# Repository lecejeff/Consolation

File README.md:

# Consolation
Consolation [Console Emulation] project goal is to create a portable emulation device 100% open-source and designed for cost effectiveness and accessibility.

Based on Raspberry Pi Compute Module 5 as core processor

Based on Raspberry Pi RP2350A as joystick controller re-using GP2040-CE FW

Based on Texas Instruments BQ25640 as USB-C PD solution and battery charger

Based on Nuvoton NAU88C22 audio codec

Consolation is a french word for:

1 : the act or an instance of consoling : the state of being consoled : comfort

2 : something that consoles

## SPONSOR

This project is proudly sponsored by [NextPCB](https://www.nextpcb.com). They have provided, free of charge, 2x assembled PCBA, as part of NextPCB accelerator program.

If you’re planning to build your own PCB, [NextPCB](https://www.nextpcb.com) offers reliable PCB fabrication and assembly services with fast turnaround times and competitive pricing, making it easier to bring your electronics projects from idea to reality.
NextPCB provides a free DFM software called NextDFM, which became, honestly, an essential tool in my toolbox, and should be the same for any serious hobbyist trying to limit PCB revisions, production back and forth, and confirm manufacturability of a design. 
NextDFM analyzes gerbers, checks Pick N Place data, validates component alignment (origin) against PnP data, validates BOM accuracy against PnP data... And also performs DFM checks for manufacturability. It's really an amazing software and it's free.

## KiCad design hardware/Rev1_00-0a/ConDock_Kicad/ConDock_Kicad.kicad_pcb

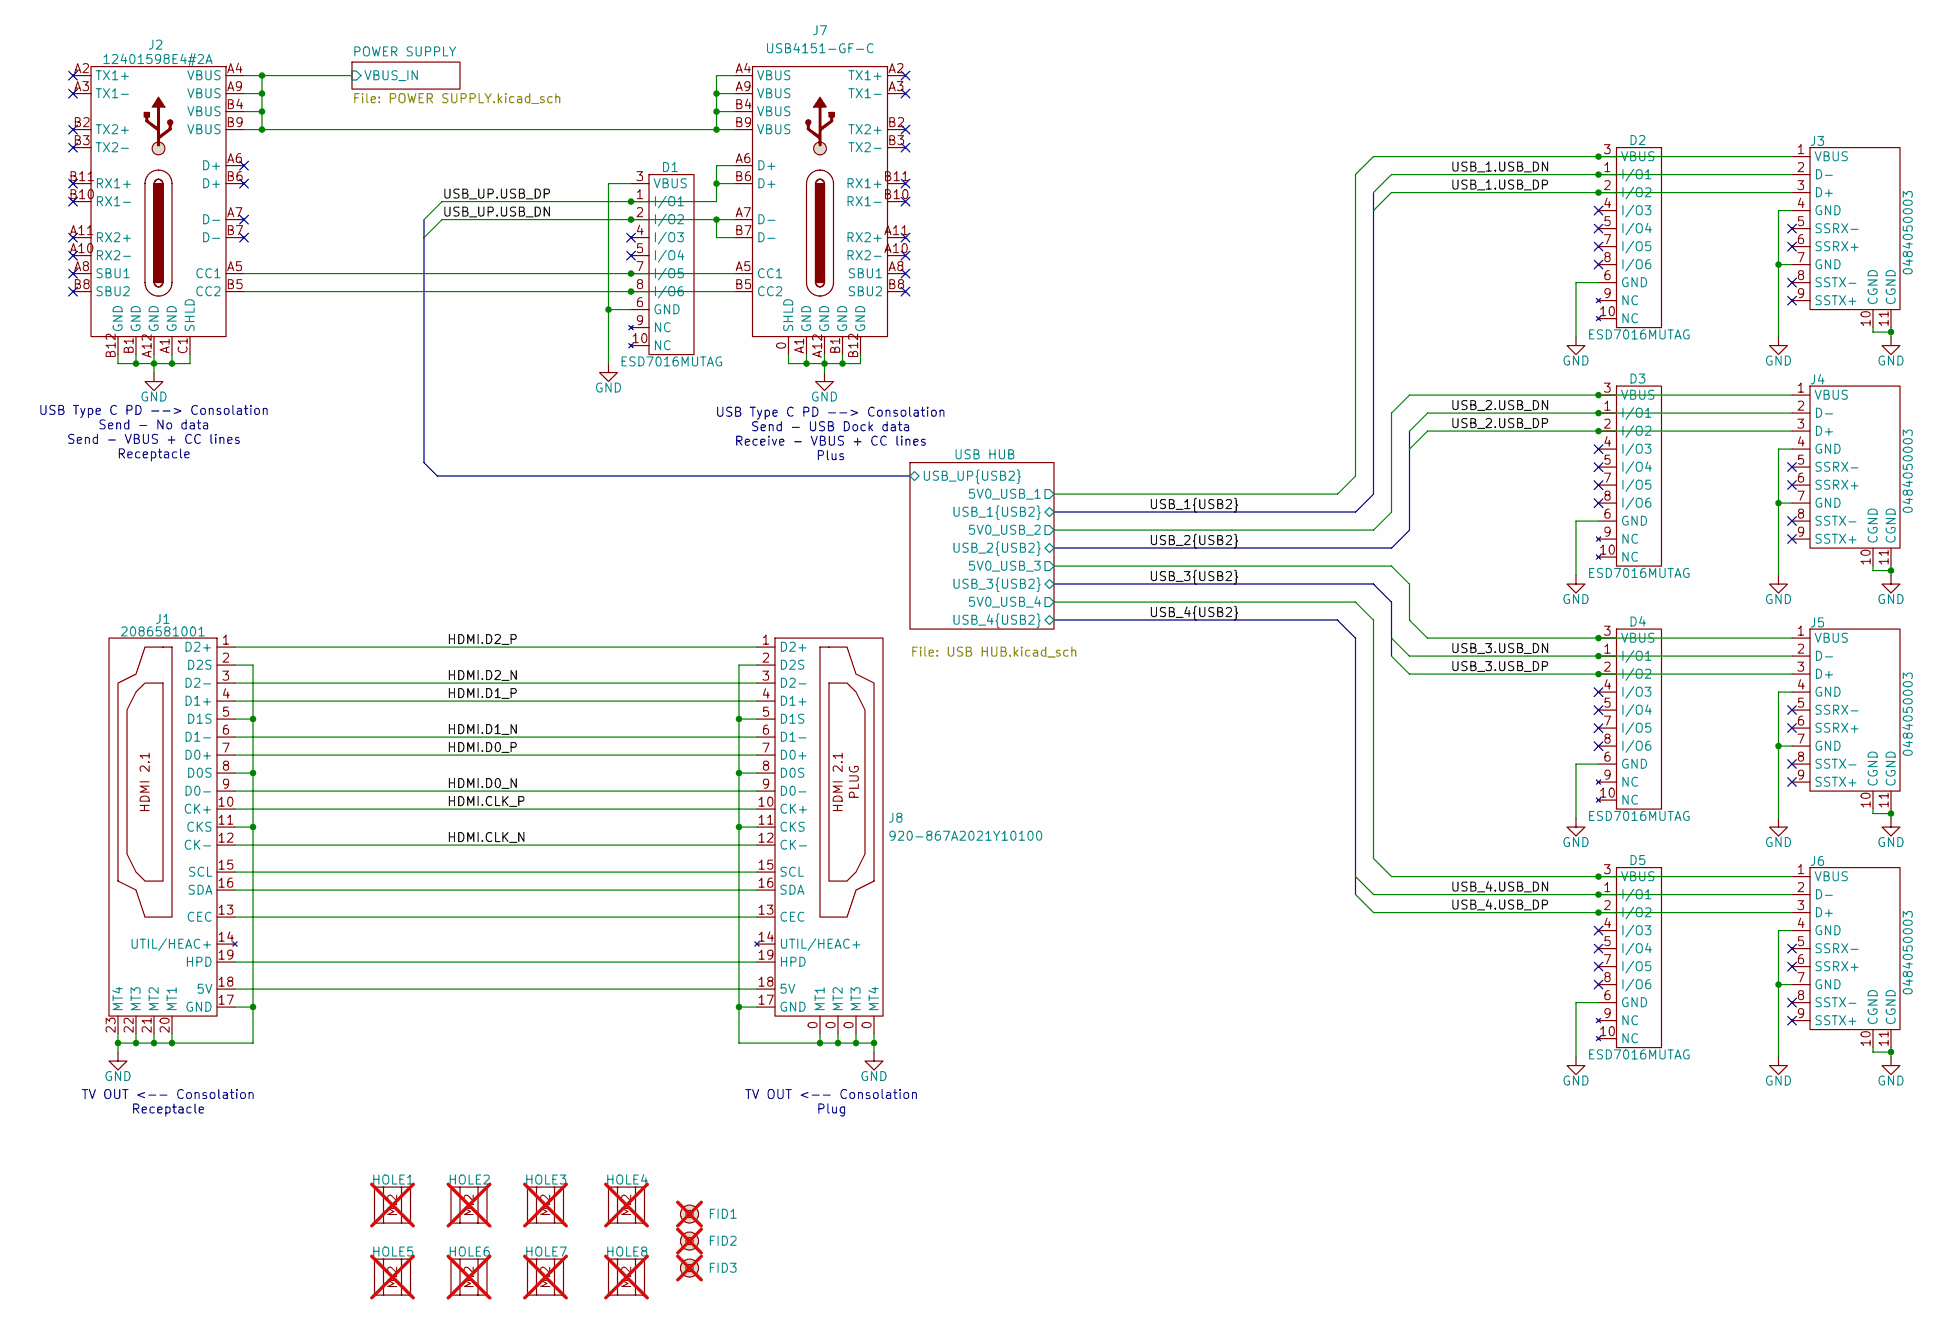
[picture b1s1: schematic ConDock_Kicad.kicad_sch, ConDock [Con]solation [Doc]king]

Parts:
D1, D2, D3, D4, D5: ESD7016MUTAG; UDFN8; Manufacturer Part Number ESD7016MUTAG
FID1, FID2, FID3: FIDUCIAL; not fitted
HOLE1, HOLE2, HOLE3, HOLE4, HOLE5, HOLE6, HOLE7, HOLE8: NPTH_M2; not fitted
J1: 2086581001; Current Rating 0.5A; Voltage Rating 40V; Manufacturer Part Number 2086581001
J2: 12401598E4#2A; Current Rating 5A; Voltage Rating 100V; Manufacturer Part Number 12401598E4#2A
J3, J4, J5, J6: 0484050003; Current Rating 1.8A; Voltage Rating 30V; Manufacturer Part Number 0484050003
J7: USB4151-GF-C; Current Rating 5A; Voltage Rating 48V; Manufacturer Part Number USB4151-GF-C
J8: 920-867A2021Y10100; Current Rating 0.5A; Voltage Rating 40V; Manufacturer Part Number 920-867A2021Y10100

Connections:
/HDMI.CLK_N: J1.12 (CK-), J8.12 (CK-)
/HDMI.CLK_P: J1.10 (CK+), J8.10 (CK+)
/HDMI.D0_N: J1.9 (D0-), J8.9 (D0-)
/HDMI.D0_P: J1.7 (D0+), J8.7 (D0+)
/HDMI.D1_N: J1.6 (D1-), J8.6 (D1-)
/HDMI.D1_P: J1.4 (D1+), J8.4 (D1+)
/HDMI.D2_N: J1.3 (D2-), J8.3 (D2-)
/HDMI.D2_P: J1.1 (D2+), J8.1 (D2+)
/POWER SUPPLY/VBUS_IN: J2.A4 (VBUS), J2.A9 (VBUS), J2.B4 (VBUS), J2.B9 (VBUS), J7.A4 (VBUS), J7.A9 (VBUS), J7.B4 (VBUS), J7.B9 (VBUS); also elsewhere on the board
/USB HUB/5V0_USB_1: D2.3 (VBUS), J3.1 (VBUS); also elsewhere on the board
/USB HUB/5V0_USB_2: D3.3 (VBUS), J4.1 (VBUS); also elsewhere on the board
/USB HUB/5V0_USB_3: D4.3 (VBUS), J5.1 (VBUS); also elsewhere on the board
/USB HUB/5V0_USB_4: D5.3 (VBUS), J6.1 (VBUS); also elsewhere on the board
/USB HUB/USB_UP.USB_DN: D1.2 (I/O2), J7.A7 (D-), J7.B7 (D-); also elsewhere on the board
/USB HUB/USB_UP.USB_DP: D1.1 (I/O1), J7.A6 (D+), J7.B6 (D+); also elsewhere on the board
/USB_1.USB_DN: D2.1 (I/O1), J3.2 (D-); also elsewhere on the board
/USB_1.USB_DP: D2.2 (I/O2), J3.3 (D+); also elsewhere on the board
/USB_2.USB_DN: D3.1 (I/O1), J4.2 (D-); also elsewhere on the board
/USB_2.USB_DP: D3.2 (I/O2), J4.3 (D+); also elsewhere on the board
/USB_3.USB_DN: D4.1 (I/O1), J5.2 (D-); also elsewhere on the board
/USB_3.USB_DP: D4.2 (I/O2), J5.3 (D+); also elsewhere on the board
/USB_4.USB_DN: D5.1 (I/O1), J6.2 (D-); also elsewhere on the board
/USB_4.USB_DP: D5.2 (I/O2), J6.3 (D+); also elsewhere on the board
GND: D1.3 (VBUS), D1.6 (GND), D2.6 (GND), D3.6 (GND), D4.6 (GND), D5.6 (GND), J1.2 (D2S), J1.5 (D1S), J1.8 (D0S), J1.11 (CKS), J1.17 (GND), J1.20 (MT1), J1.21 (MT2), J1.22 (MT3), J1.23 (MT4), J2.A1 (GND), J2.A12 (GND), J2.B1 (GND), J2.B12 (GND), J2.C1 (SHLD), J3.4 (GND), J3.7 (GND), J3.10 (CGND), J3.11 (CGND), J4.4 (GND), J4.7 (GND), J4.10 (CGND), J4.11 (CGND), J5.4 (GND), J5.7 (GND), J5.10 (CGND), J5.11 (CGND), J6.4 (GND), J6.7 (GND), J6.10 (CGND), J6.11 (CGND), J7.0 (SHLD), J7.A1 (GND), J7.A12 (GND), J7.B1 (GND), J7.B12 (GND), J8.0 (MT4), J8.2 (D2S), J8.5 (D1S), J8.8 (D0S), J8.11 (CKS), J8.17 (GND); also elsewhere on the board
unnamed: D1.7 (I/O5), J2.A5 (CC1), J7.A5 (CC1)
unnamed: D1.8 (I/O6), J2.B5 (CC2), J7.B5 (CC2)
unnamed: J1.18 (5V), J8.18 (5V)
unnamed: J1.13 (CEC), J8.13 (CEC)
unnamed: J1.19 (HPD), J8.19 (HPD)
unnamed: J1.15 (SCL), J8.15 (SCL)
unnamed: J1.16 (SDA), J8.16 (SDA)

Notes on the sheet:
USB Type C PD --> Consolation Send - USB Dock data Receive - VBUS + CC lines Plus
TV OUT <-- Consolation Receptacle
TV OUT <-- Consolation Plug
USB Type C PD --> Consolation Send - No data Send - VBUS + CC lines Receptacle

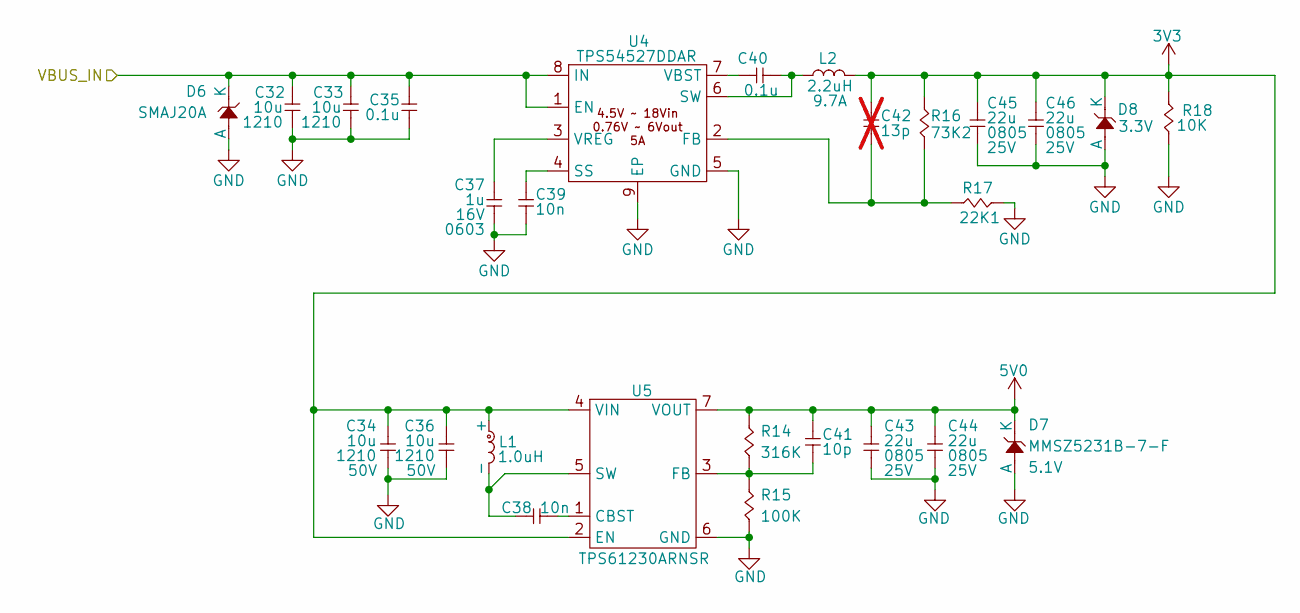
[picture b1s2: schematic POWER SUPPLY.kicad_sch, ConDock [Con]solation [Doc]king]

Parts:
C32, C33: 10u; CAP_NONPOL_1210; Tolerance ±10%; Voltage Rating 50V; Manufacturer Part Number C3225X7R1H106K250AC
C34, C36: 10u; CAP_NONPOL_1210; Tolerance ±10%; Voltage Rating 50V; Manufacturer Part Number CNC6P1X7R1H106K250AE
C35, C40: 0.1u; CAP_NONPOL_0402; Tolerance ±10%; Voltage Rating 50V; Manufacturer Part Number GRM155R71H104KE14D
C37: 1u; CAP_NONPOL_0603; Tolerance ±10%; Voltage Rating 16V; Manufacturer Part Number CC0603KRX7R7BB105
C38, C39: 10n; CAP_NONPOL_0402; Tolerance ±10%; Voltage Rating 50V; Manufacturer Part Number GCM155R71H103KA55D
C41: 10p; CAP_NONPOL_0402; Tolerance ±5%; Voltage Rating 50V; Manufacturer Part Number CC0402JRNPO9BN100
C42: 13p; CAP_NONPOL_0402; Tolerance ±2%; Voltage Rating 50V; Manufacturer Part Number GJM1555C1H130GB01D; not fitted
C43, C44: 22u; CAP_NONPOL_0805; Tolerance ±20%; Voltage Rating 25V; Manufacturer Part Number GMC21X5R226M25NT
C45, C46: 22u; CAP_NONPOL_0805; Tolerance ±20%; Voltage Rating 25V; Manufacturer Part Number CL21A226MAYNNNE
D6: SMAJ20A; DO-214AC; Tolerance NA; Manufacturer Part Number SMAJ20A
D7: MMSZ5231B-7-F; SOD-123; Tolerance ±5%; Manufacturer Part Number MMSZ5231B-7-F
D8: MMSZ5226B; SOD-123; Tolerance ±5%; Manufacturer Part Number MMSZ5226B-7-F
L1: PA5003.102NLT; PA5003; Tolerance ±20%; Manufacturer Part Number PA5003.102NLT
L2: PA5003.222NLT; PA5003; Tolerance ±20%; Manufacturer Part Number PA5003.222NLT
R14: 316K; RES_0402; Tolerance 1%; Manufacturer Part Number RC0402FR-13316KL
R15: 100K; RES_0402; Tolerance 1%; Manufacturer Part Number RC0402FR-07100KL
R16: 73K2; RES_0402; Tolerance 1%; Manufacturer Part Number RC0402FR-0773K2L
R17: 22K1; RES_0402; Tolerance 1%; Manufacturer Part Number RC0402FR-0722K1L
R18: 10K; RES_0402; Tolerance 1%; Manufacturer Part Number RC0402FR-0710KL
U4: TPS54527DDAR; SO-8-150mil-EP; Input Voltage (Min) 4.5V; Input Voltage (Max) 18V; Manufacturer Part Number TPS54527DDAR
U5: TPS61230ARNSR; VQFN-7; Input Voltage (Min) 2.5V; Output Voltage 2.5V ~ 5.5V; Manufacturer Part Number TPS61230ARNSR

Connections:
3V3: C34.2, C36.2, C42.2, C45.2, C46.2, D8.1 (K), L1.1 (+), L2.2, R16.2, R18.2, U5.2 (EN), U5.4 (VIN); also elsewhere on the board
5V0: C41.2, C43.2, C44.2, D7.1 (K), R14.2, U5.7 (VOUT); also elsewhere on the board
/POWER SUPPLY/VBUS_IN: C32.2, C33.2, C35.2, D6.1 (K), U4.1 (EN), U4.8 (IN); also elsewhere on the board
GND: C32.1, C33.1, C34.1, C35.1, C36.1, C37.1, C39.1, C43.1, C44.1, C45.1, C46.1, D6.2 (A), D7.2 (A), D8.2 (A), R15.1, R17.2, R18.1, U4.5 (GND), U4.9 (EP), U5.6 (GND); also elsewhere on the board
unnamed: C38.1, L1.2 (-), U5.5 (SW)
unnamed: C42.1, R16.1, R17.1, U4.2 (FB)
unnamed: C39.2, U4.4 (SS)
unnamed: C40.1, L2.1, U4.6 (SW)
unnamed: C40.2, U4.7 (VBST)
unnamed: C37.2, U4.3 (VREG)
unnamed: C38.2, U5.1 (CBST)
unnamed: C41.1, R14.1, R15.2, U5.3 (FB)

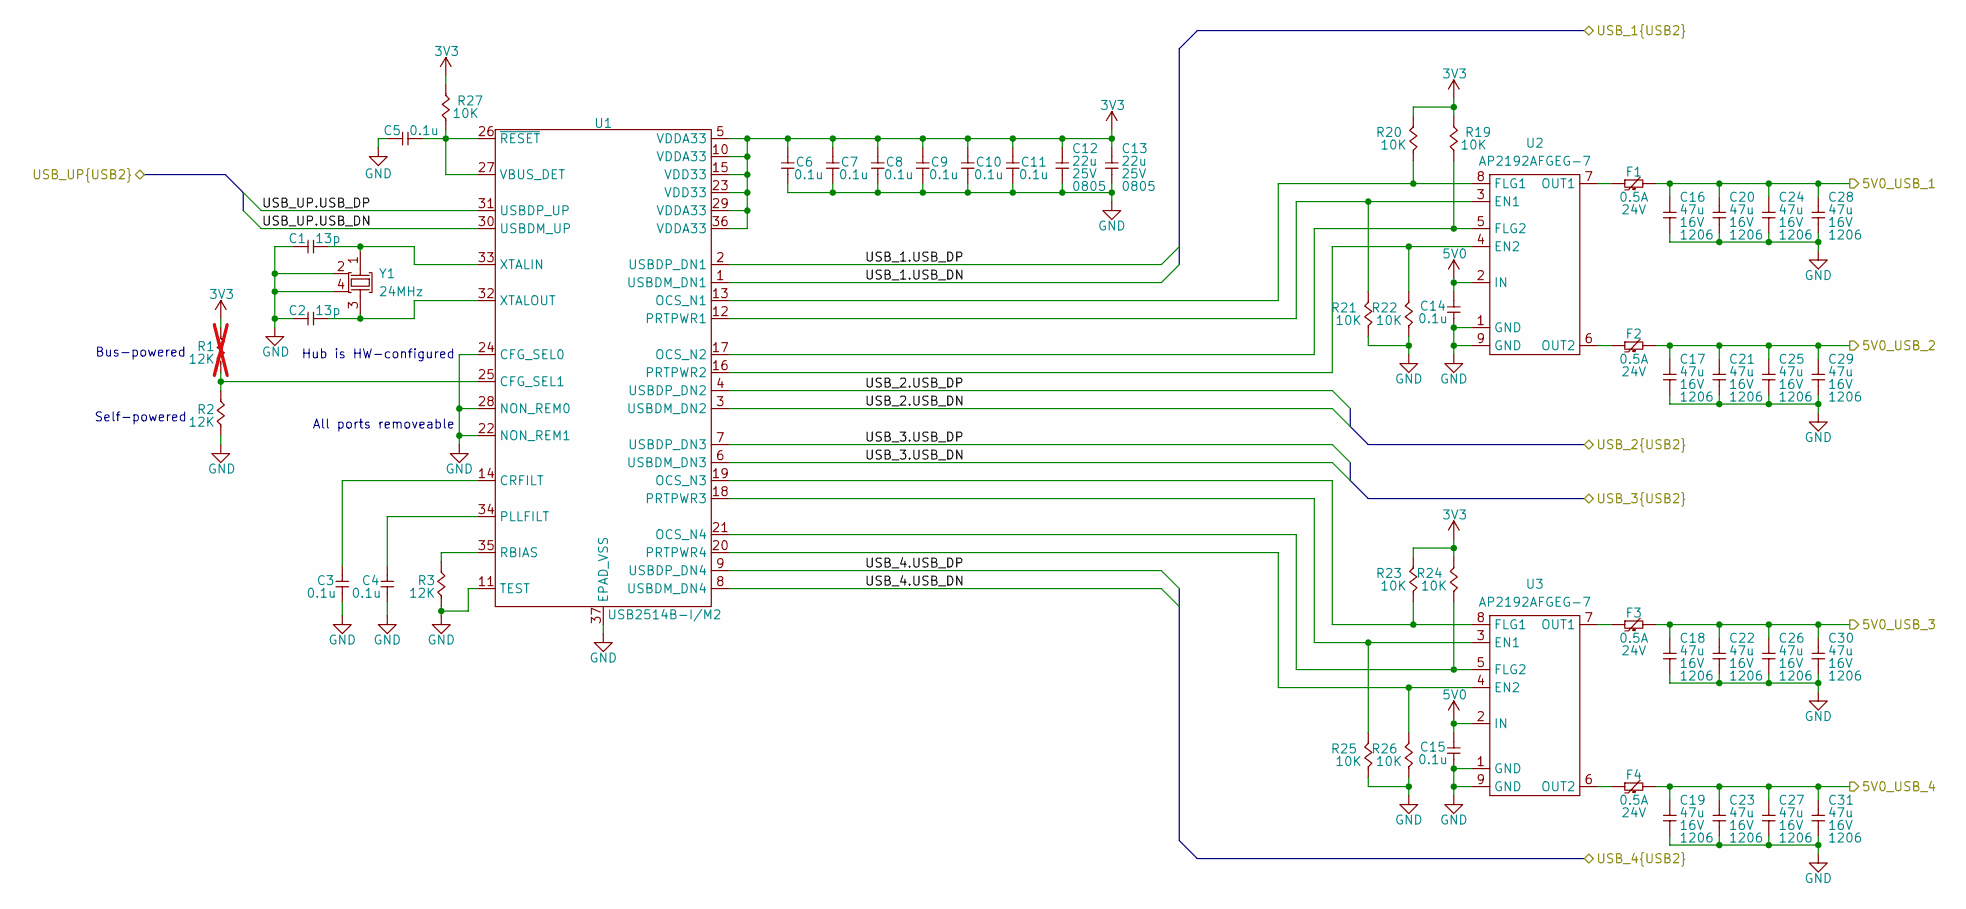
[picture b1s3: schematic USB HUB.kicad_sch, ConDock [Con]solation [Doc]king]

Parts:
C1, C2: 13p; CAP_NONPOL_0402; Tolerance ±2%; Voltage Rating 50V; Manufacturer Part Number GJM1555C1H130GB01D
C3, C4, C5, C6, C7, C8, C9, C10, C11, C14, C15: 0.1u; CAP_NONPOL_0402; Tolerance ±10%; Voltage Rating 50V; Manufacturer Part Number GRM155R71H104KE14D
C12, C13: 22u; CAP_NONPOL_0805; Tolerance ±20%; Voltage Rating 25V; Manufacturer Part Number GMC21X5R226M25NT
C16, C17, C18, C19, C20, C21, C22, C23, C24, C25, C26, C27, C28, C29, C30, C31: 47u; CAP_NONPOL_1206; Tolerance ±20%; Voltage Rating 16V; Manufacturer Part Number C3216X5R1C476M160AB
F1, F2, F3, F4: MINISMDC050F-2; PTC_1812; Voltage 24V; Manufacturer Part Number MINISMDC050F-2
R1: 12K; RES_0402; Tolerance 1%; Manufacturer Part Number RC0402FR-1312KL; not fitted
R2, R3: 12K; RES_0402; Tolerance 1%; Manufacturer Part Number RC0402FR-1312KL
R19, R20, R21, R22, R23, R24, R25, R26, R27: 10K; RES_0402; Tolerance 1%; Manufacturer Part Number RC0402FR-0710KL
U1: USB2514B-I/M2; 36-SQFN; Supply Voltage 3.0 ~ 3.6V; Manufacturer Part Number USB2514B-I/M2
U2, U3: AP2192AFGEG-7; U-DFN3030-8; Load Voltage 2.7V ~ 5.5V; Manufacturer Part Number AP2192AFGEG-7
Y1: 24MHz; 4-SMD_2mmx1_6mm; Tolerance ±20ppm; Manufacturer Part Number ABM11-24.000MHZ-D2X-T3

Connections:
3V3: C6.2, C7.2, C8.2, C9.2, C10.2, C11.2, C12.2, C13.2, R1.2, R19.2, R20.2, R23.2, R24.2, R27.2, U1.5 (VDDA33), U1.10 (VDDA33), U1.15 (VDD33), U1.23 (VDD33), U1.29 (VDDA33), U1.36 (VDDA33); also elsewhere on the board
5V0: C14.2, C15.2, U2.2 (IN), U3.2 (IN); also elsewhere on the board
/USB HUB/5V0_USB_1: C16.2, C20.2, C24.2, C28.2, F1.2; also elsewhere on the board
/USB HUB/5V0_USB_2: C17.2, C21.2, C25.2, C29.2, F2.2; also elsewhere on the board
/USB HUB/5V0_USB_3: C18.2, C22.2, C26.2, C30.2, F3.2; also elsewhere on the board
/USB HUB/5V0_USB_4: C19.2, C23.2, C27.2, C31.2, F4.2; also elsewhere on the board
/USB HUB/USB_UP.USB_DN: U1.30 (USBDM_UP); also elsewhere on the board
/USB HUB/USB_UP.USB_DP: U1.31 (USBDP_UP); also elsewhere on the board
/USB_1.USB_DN: U1.1 (USBDM_DN1); also elsewhere on the board
/USB_1.USB_DP: U1.2 (USBDP_DN1); also elsewhere on the board
/USB_2.USB_DN: U1.3 (USBDM_DN2); also elsewhere on the board
/USB_2.USB_DP: U1.4 (USBDP_DN2); also elsewhere on the board
/USB_3.USB_DN: U1.6 (USBDM_DN3); also elsewhere on the board
/USB_3.USB_DP: U1.7 (USBDP_DN3); also elsewhere on the board
/USB_4.USB_DN: U1.8 (USBDM_DN4); also elsewhere on the board
/USB_4.USB_DP: U1.9 (USBDP_DN4); also elsewhere on the board
GND: C1.1, C2.1, C3.1, C4.1, C5.2, C6.1, C7.1, C8.1, C9.1, C10.1, C11.1, C12.1, C13.1, C14.1, C15.1, C16.1, C17.1, C18.1, C19.1, C20.1, C21.1, C22.1, C23.1, C24.1, C25.1, C26.1, C27.1, C28.1, C29.1, C30.1, C31.1, R2.1, R3.1, R21.1, R22.1, R25.1, R26.1, U1.11 (TEST), U1.22 (NON_REM1), U1.24 (CFG_SEL0), U1.28 (NON_REM0), U1.37 (EPAD_VSS), U2.1 (GND), U2.9 (GND), U3.1 (GND), U3.9 (GND), Y1.2 (GND), Y1.4 (GND); also elsewhere on the board
unnamed: R1.1, R2.2, U1.25 (CFG_SEL1)
unnamed: C3.2, U1.14 (CRFILT)
unnamed: R20.1, U1.13 (OCS_N1), U2.8 (FLG1)
unnamed: R19.1, U1.17 (OCS_N2), U2.5 (FLG2)
unnamed: R23.1, U1.19 (OCS_N3), U3.8 (FLG1)
unnamed: R24.1, U1.21 (OCS_N4), U3.5 (FLG2)
unnamed: C4.2, U1.34 (PLLFILT)
unnamed: R21.2, U1.12 (PRTPWR1), U2.3 (EN1)
unnamed: R22.2, U1.16 (PRTPWR2), U2.4 (EN2)
unnamed: R25.2, U1.18 (PRTPWR3), U3.3 (EN1)
unnamed: R26.2, U1.20 (PRTPWR4), U3.4 (EN2)
unnamed: R3.2, U1.35 (RBIAS)
unnamed: C5.1, R27.1, U1.26 (~RESET), U1.27 (VBUS_DET)
unnamed: C1.2, U1.33 (XTALIN), Y1.1 (XI)
unnamed: C2.2, U1.32 (XTALOUT), Y1.3 (XO)
unnamed: F1.1, U2.7 (OUT1)
unnamed: F2.1, U2.6 (OUT2)
unnamed: F3.1, U3.7 (OUT1)
unnamed: F4.1, U3.6 (OUT2)

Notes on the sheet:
Bus-powered
Self-powered
All ports removeable
Hub is HW-configured

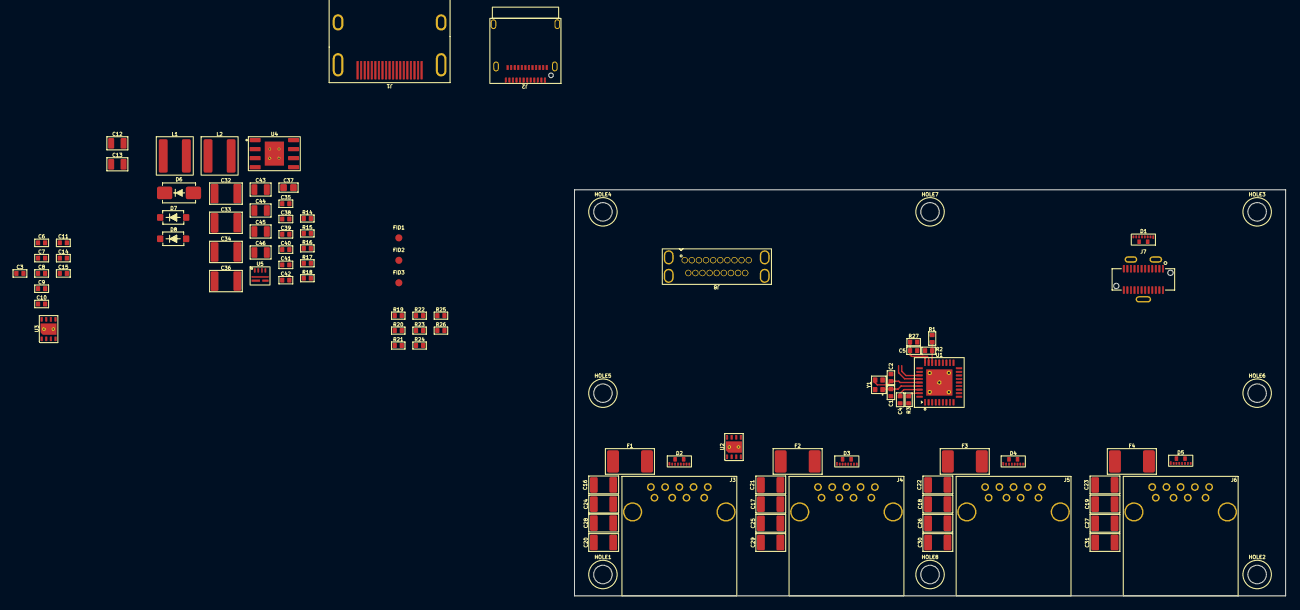
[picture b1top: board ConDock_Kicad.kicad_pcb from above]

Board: 2 copper layers, 100.0 x 57.1 mm, 102 parts (0 on the bottom side), 60 nets.

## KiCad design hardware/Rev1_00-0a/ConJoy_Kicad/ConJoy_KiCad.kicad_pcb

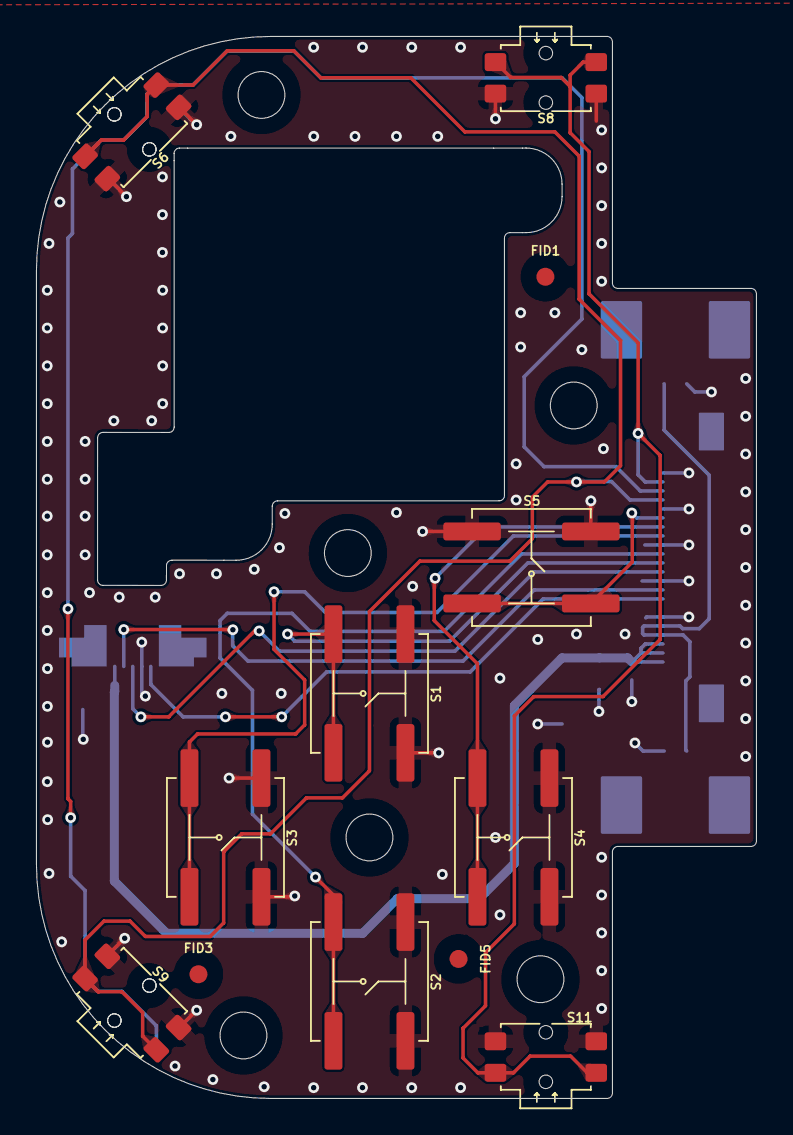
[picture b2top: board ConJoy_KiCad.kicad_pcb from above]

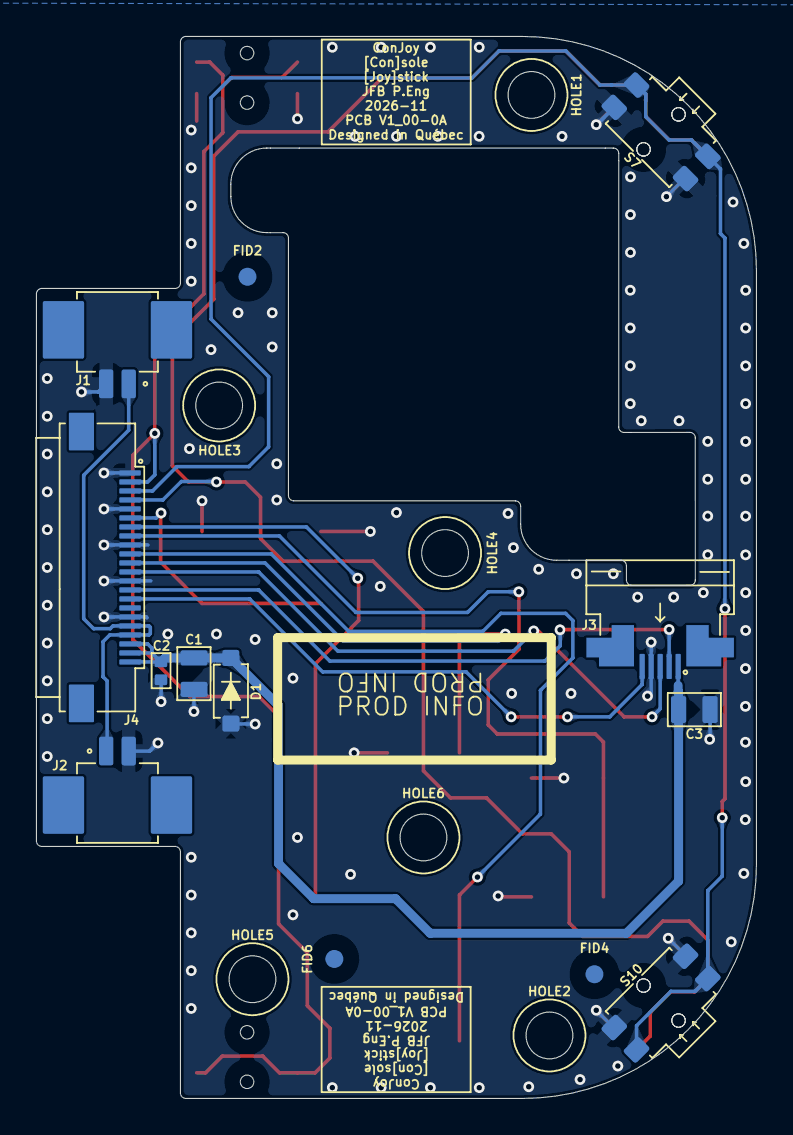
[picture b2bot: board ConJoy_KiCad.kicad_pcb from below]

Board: 2 copper layers, 40.0 x 59.0 mm, 31 parts (19 on the bottom side), 14 nets.

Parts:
C1, C3: 1u; CAP_NONPOL_0805
C2: 0.1u; CAP_NONPOL_0402
D1: MMSZ5226B-7-F; SOD-123
FID1, FID2, FID3, FID4, FID5, FID6: FIDUCIAL
HOLE1, HOLE2, HOLE3, HOLE4, HOLE5, HOLE6: NPTH_M2
J1, J2: 0532610271
J3: SFV5R-1STE1HLF; SFV5R-1ST
J4: 5051102291
S1, S2, S3, S4, S5: EVQ-Q2P03W; EVQQ2
S6, S7, S8, S9, S10, S11: TL1014BF160QG; TL1014B

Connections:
3V3: C1.2, C2.2, C3.2, D1.1 (K), J3.1, J4.20, J4.21, J4.22
/L_DPAD_DOWN/R_BTN_B: J4.10, S2.2
/L_DPAD_LEFT/R_BTN_X: J4.8, S3.2
/L_DPAD_RIGHT/R_BTN_Y: J4.7, S4.2
/L_DPAD_UP/R_BTN_A: J4.11, S1.2
/L_HOME/R_EXTRA: J4.2, S8.2, S11.2
/L_R_L1_TRIG: J4.4, S6.2, S9.2
/L_R_L2_TRIG: J4.3, S7.2, S10.2
/L_R_SPKOUT: J1.1, J2.1, J4.18, J4.19
/L_R_THUMBST_SW: J3.3, J4.12
/L_R_THUMBST_X: J3.5, J4.15
/L_R_THUMBST_Y: J3.2, J4.14
/L_START/R_SELECT: J4.6, S5.2
GND: C1.1, C2.1, C3.1, D1.2 (A), J1.2, J2.2, J3.4, J4.1, J4.5, J4.9, J4.13, J4.17, S1.1, S2.1, S3.1, S4.1, S5.1, S6.1, S7.1, S8.1, S9.1, S10.1, S11.1
